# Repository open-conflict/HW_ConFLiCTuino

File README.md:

HW_ConFLiCTuino
===============

<br>
<b>ConFLiCTuino 0.6: </b><br>
 <br>
 - changed PWM1 and PWM2 Header to the correct molex footprint. <br>
 - no electrical changes to 0.5 <br>
     <br>
 <br>
<b>ConFLiCTuino 0.5: </b><br>
 <br>
 - add 1-wire header  <br>
 - firmware compatible to 0.2, except of 1-Wire functionallity <br>
     <br>
 <br>
<b>ConFLiCTuino 0.4: </b><br>
 <br>
 - rework complete Layout for smaller size  <br>
 - changed resistor package to reduce part and assembly costs <br>
 - firmware compatible to 0.2 <br>
     <br>
 <br>
<b>ConFLiCTuino 0.3: </b><br>
 <br>
 - changed D1 and D3 to S1D type in DO214AC package  <br>
 - firmware compatible to 0.2 <br>
     <br>
 <br>
<b>ConFLiCTuino 0.2:  </b>   <br>
  <br>
 - changed pin mapping to arduino to use hardware functions     <br>
 - changed whole layout to match new pin mapping   <br>
 <br>
 <br>
<b>ConFLiCTuino 0.1:   </b> <br>
  <br>
 - first version     <br>

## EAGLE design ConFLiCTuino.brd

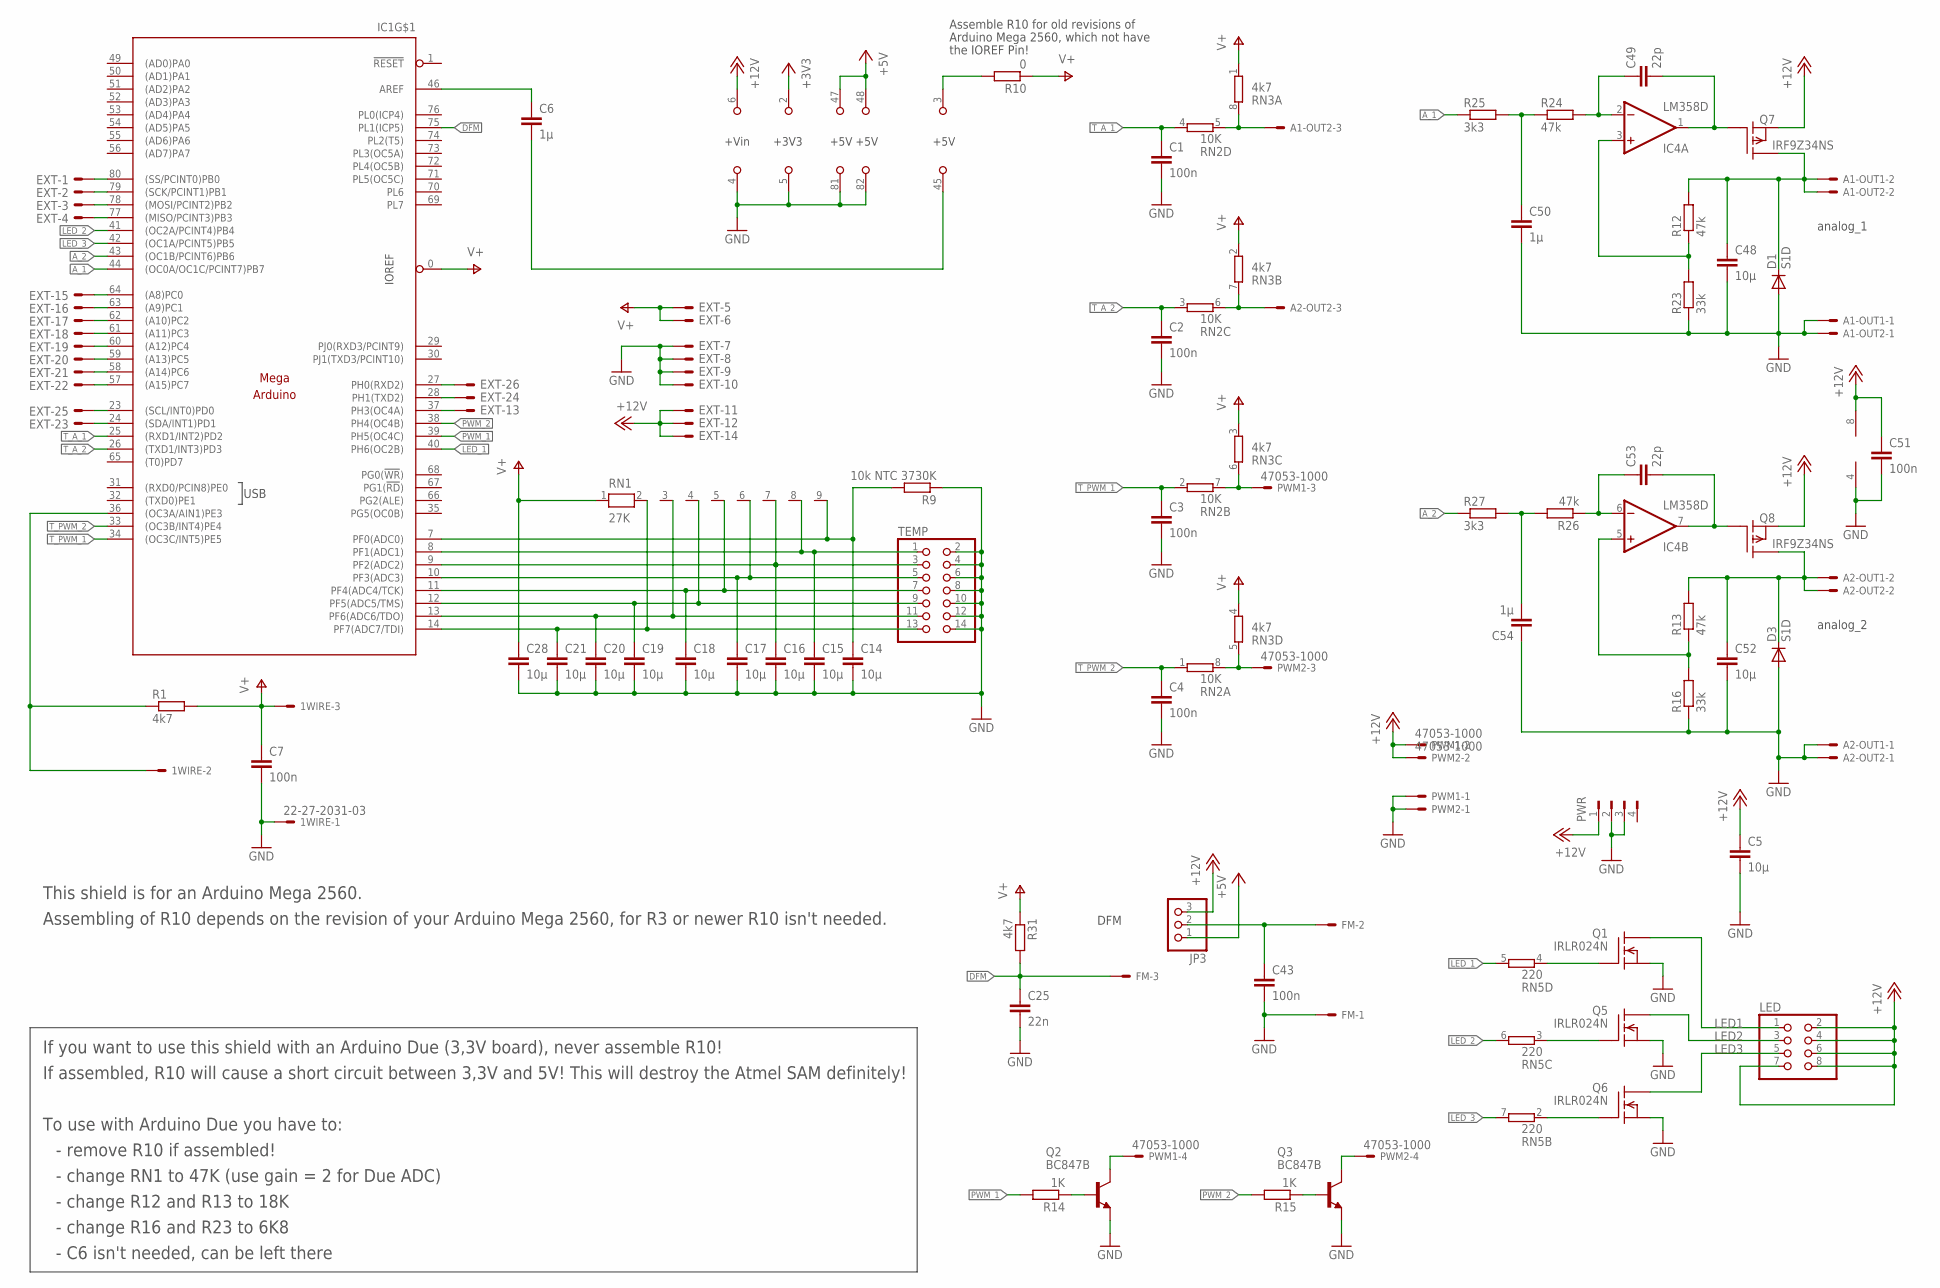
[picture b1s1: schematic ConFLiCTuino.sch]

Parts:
1WIRE: 22-27-2031-03; 6410-03
A1-OUT1, A1-OUT2, A2-OUT1, A2-OUT2: 22-27-2031-03; 6410-03
C1, C2, C3, C4, C7, C43, C51: 100n; C0805K
C5, C14, C15, C16, C17, C18, C19, C20, C21, C28, C48, C52: 10µ; C0805K
C6, C50, C54: 1µ; C0805K
C25: 22n; C0805K
C49, C53: 22p; C0805K
D1, D3: S1D; DO214AC
EXT: ML26E; ML26
FM: 22-27-2031-03; 6410-03
IC1: MEGAARDUINO_CUSTOM; ARDUINO_MEGA_R3_SMALL_CUSTOM
IC4: LM358D; SO08
JP3: PINHD-1X3; 1X03
LED: PINHD-2X4; 2X04
PWM1, PWM2: 47053-1000
PWR: FLOPPY-4350211; 350211
Q1, Q5, Q6: IRLR024N; DPACK
Q2, Q3: BC847B; SOT23
Q7, Q8: IRF9Z34NS; D2PACK
R1, R31: 4k7; M0805
R9: 10k NTC 3730K; M0805
R10: 0; M0805
R12, R13, R24, R26: 47k; M0805
R14, R15: 1K; M0805
R16, R23: 33k; M0805
R25, R27: 3k3; M0805
RN1: 27K; RN-9
RN2: 10K; CAT16
RN3: 4k7; CAT16
RN5: 220; CAT16
TEMP: PINHD-2X7; 2X07

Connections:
+3V3: IC1.2 (+3V3)
+5V: IC1.47 (+5V), IC1.48 (+5V), JP3.1
+12V: C5.1, C51.1, EXT.11, EXT.12, EXT.14, IC1.6 (+VIN), IC4.8 (V+), JP3.3, LED.2, LED.4, LED.6, LED.7, LED.8, PWM1.2, PWM2.2, PWR.1, Q7.3 (S), Q8.3 (S)
A_1: IC1.44 ((OC0A/OC1C/PCINT7)PB7), R25.1
A_2: IC1.43 ((OC1B/PCINT6)PB6), R27.1
DFM: C25.1, FM.3, IC1.75 (PL1(ICP5)), R31.2
GND: 1WIRE.1, A1-OUT1.1, A1-OUT2.1, A2-OUT1.1, A2-OUT2.1, C1.2, C2.2, C3.2, C4.2, C5.2, C7.2, C14.2, C15.2, C16.2, C17.2, C18.2, C19.2, C20.2, C21.2, C25.2, C28.2, C43.2, C48.2, C50.2, C51.2, C52.2, C54.1, D1.A, D3.A, EXT.7, EXT.8, EXT.9, EXT.10, FM.1, IC1.4 (GND), IC1.5 (GND), IC1.81 (GND), IC1.82 (GND), IC4.4 (V-), PWM1.1, PWM2.1, PWR.2, PWR.3, Q1.3 (S), Q2.2 (E), Q3.2 (E), Q5.3 (S), Q6.3 (S), R9.1, R16.1, R23.1, TEMP.2, TEMP.4, TEMP.6, TEMP.8, TEMP.10, TEMP.12, TEMP.14
LED1: LED.1, Q1.4 (D)
LED2: LED.3, Q5.4 (D)
LED3: LED.5, Q6.4 (D)
LED_1: IC1.40 (PH6(OC2B)), RN5.5 (2)
LED_2: IC1.41 ((OC2A/PCINT4)PB4), RN5.6 (2)
LED_3: IC1.42 ((OC1A/PCINT5)PB5), RN5.7 (2)
unnamed: EXT.23, IC1.24 ((SDA/INT1)PD1)
unnamed: A1-OUT2.3, RN2.5 (2), RN3.8 (2)
unnamed: A2-OUT1.2, A2-OUT2.2, C52.1, D3.C, Q8.2 (D), R13.2
unnamed: EXT.24, IC1.28 (PH1(TXD2))
unnamed: A2-OUT2.3, RN2.6 (2), RN3.7 (2)
unnamed: IC4.3 (+IN), R12.1, R23.2
unnamed: EXT.25, IC1.23 ((SCL/INT0)PD0)
unnamed: C49.2, IC4.1 (OUT), Q7.1 (G)
unnamed: EXT.26, IC1.27 (PH0(RXD2))
unnamed: EXT.22, IC1.57 ((A15)PC7)
unnamed: C43.1, FM.2, JP3.2
unnamed: PWM1.3, RN2.7 (2), RN3.6 (2)
unnamed: EXT.21, IC1.58 ((A14)PC6)
unnamed: PWM2.3, RN2.8 (2), RN3.5 (2)
unnamed: EXT.20, IC1.59 ((A13)PC5)
unnamed: IC4.5 (+IN), R13.1, R16.2
unnamed: EXT.19, IC1.60 ((A12)PC4)
unnamed: C49.1, IC4.2 (-IN), R24.2
unnamed: Q2.1 (B), R14.1
unnamed: A1-OUT1.2, A1-OUT2.2, C48.1, D1.C, Q7.2 (D), R12.2
unnamed: Q3.1 (B), R15.1
unnamed: PWM1.4, Q2.3 (C)
unnamed: EXT.18, IC1.61 ((A11)PC3)
unnamed: C53.2, IC4.7 (OUT), Q8.1 (G)
unnamed: PWM2.4, Q3.3 (C)
unnamed: EXT.17, IC1.62 ((A10)PC2)
unnamed: EXT.16, IC1.63 ((A9)PC1)
unnamed: EXT.15, IC1.64 ((A8)PC0)
unnamed: EXT.2, IC1.79 ((SCK/PCINT1)PB1)
unnamed: EXT.1, IC1.80 ((SS/PCINT0)PB0)
unnamed: EXT.4, IC1.77 ((MISO/PCINT3)PB3)
unnamed: EXT.3, IC1.78 ((MOSI/PCINT2)PB2)
unnamed: C14.1, IC1.7 (PF0(ADC0)), R9.2, RN1.9
unnamed: C15.1, IC1.8 (PF1(ADC1)), RN1.8, TEMP.1
unnamed: C16.1, IC1.9 (PF2(ADC2)), RN1.7, TEMP.3
unnamed: C17.1, IC1.10 (PF3(ADC3)), RN1.6, TEMP.5
unnamed: C18.1, IC1.11 (PF4(ADC4/TCK)), RN1.5, TEMP.7
unnamed: C19.1, IC1.12 (PF5(ADC5/TMS)), RN1.4, TEMP.9
unnamed: C20.1, IC1.13 (PF6(ADC6/TDO)), RN1.3, TEMP.11
unnamed: C21.1, IC1.14 (PF7(ADC7/TDI)), RN1.2, TEMP.13
unnamed: EXT.13, IC1.37 (PH3(OC4A))
unnamed: C6.1, IC1.46 (AREF)
unnamed: C6.2, IC1.45 (GND)
unnamed: 1WIRE.2, IC1.36 ((OC3A/AIN1)PE3), R1.1
unnamed: C50.1, R24.1, R25.2
unnamed: C53.1, IC4.6 (-IN), R26.1
unnamed: C54.2, R26.2, R27.2
unnamed: Q6.1 (G), RN5.2 (1)
unnamed: Q5.1 (G), RN5.3 (1)
unnamed: Q1.1 (G), RN5.4 (1)
PWM_1: IC1.39 (PH5(OC4C)), R14.2
PWM_2: IC1.38 (PH4(OC4B)), R15.2
S$2: IC1.3 (+5V), R10.2
T_A_1: C1.1, IC1.25 ((RXD1/INT2)PD2), RN2.4 (1)
T_A_2: C2.1, IC1.26 ((TXD1/INT3)PD3), RN2.3 (1)
T_PWM_1: C3.1, IC1.34 ((OC3C/INT5)PE5), RN2.2 (1)
T_PWM_2: C4.1, IC1.33 ((OC3B/INT4)PE4), RN2.1
V+: 1WIRE.3, C7.1, C28.1, EXT.5, EXT.6, IC1.0 (IOREF), R1.2, R10.1, R31.1, RN1.1, RN3.1, RN3.2 (1), RN3.3 (1), RN3.4 (1)

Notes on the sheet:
analog_2
analog_1
DFM
Assemble R10 for old revisions of
Arduino Mega 2560, which not have
the IOREF Pin!
This shield is for an Arduino Mega 2560.
Assembling of R10 depends on the revision of your Arduino Mega 2560, for R3 or newer R10 isn't needed.
If you want to use this shield with an Arduino Due (3,3V board), never assemble R10!
If assembled, R10 will cause a short circuit between 3,3V and 5V! This will destroy the Atmel SAM definitely!
To use with Arduino Due you have to:
- change RN1 to 47K (use gain = 2 for Due ADC)
- change R12 and R13 to 18K
- change R16 and R23 to 6K8
- C6 isn't needed, can be left there
- remove R10 if assembled!
USB

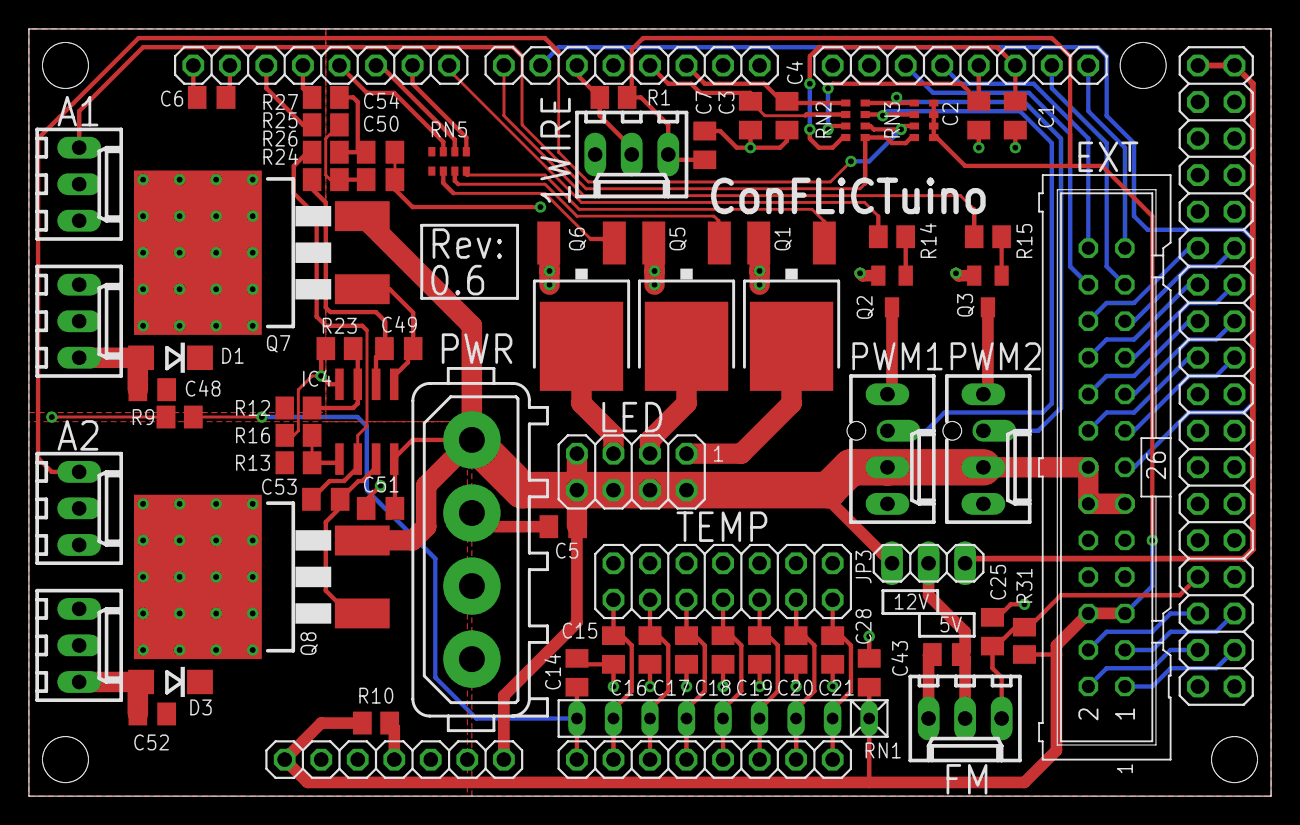
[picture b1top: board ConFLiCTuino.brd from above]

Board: 2 copper layers, 86.4 x 53.3 mm, 67 parts (0 on the bottom side), 70 nets.

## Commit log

2014-04-09 Init V0.2
2014-04-09 init V0.3
2014-04-09 edit README
2014-04-23 Init V0.4
    Changed whole layout. More resistor nets and smaller board.
2014-05-01 init V0.5
    Added 1-Wire header
2014-05-01 Update of readme
2014-05-04 Changed some packages
2014-05-04 Schaltplan schick gemacht
2014-05-11 weiter gearbeitet
    Layout noch nicht fertig
2014-05-11 warnings in ERC checked
    only uneccessarry things
2014-05-17 partlist updated to V0.5
    Added new tab in excel with the partlist for the V0.5 board
2014-05-24 init V0.6
    Changed 4-Pol PWM connectors to Molex-Footprint with hole for the kex
    pin.
